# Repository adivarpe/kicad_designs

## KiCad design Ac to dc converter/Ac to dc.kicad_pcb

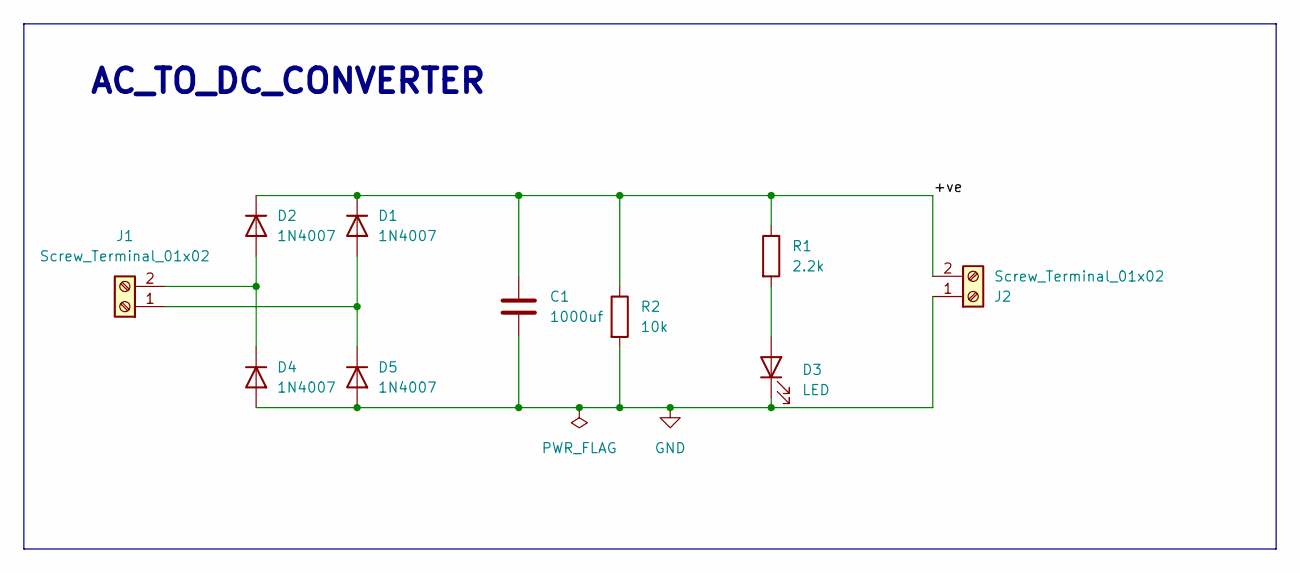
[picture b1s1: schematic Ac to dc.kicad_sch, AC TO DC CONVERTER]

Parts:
C1: 1000uf; CP_Radial_D4.0mm_P2.00mm
D1, D2, D4, D5: 1N4007; D_DO-41_SOD81_P10.16mm_Horizontal
D3: LED; LED_D3.0mm
J1, J2: Screw_Terminal_01x02; TerminalBlock_4Ucon_1x02_P3.50mm_Vertical
R1: 2.2k; R_Axial_DIN0207_L6.3mm_D2.5mm_P10.16mm_Horizontal
R2: 10k; R_Axial_DIN0207_L6.3mm_D2.5mm_P10.16mm_Horizontal

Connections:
/+ve: C1.1, D1.1 (K), D2.1 (K), J2.2, R1.1, R2.1
GND: C1.2, D3.1 (K), D4.2 (A), D5.2 (A), J2.1, R2.2
unnamed: D1.2 (A), D5.1 (K), J1.1
unnamed: D2.2 (A), D4.1 (K), J1.2
unnamed: D3.2 (A), R1.2

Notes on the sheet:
AC_TO_DC_CONVERTER

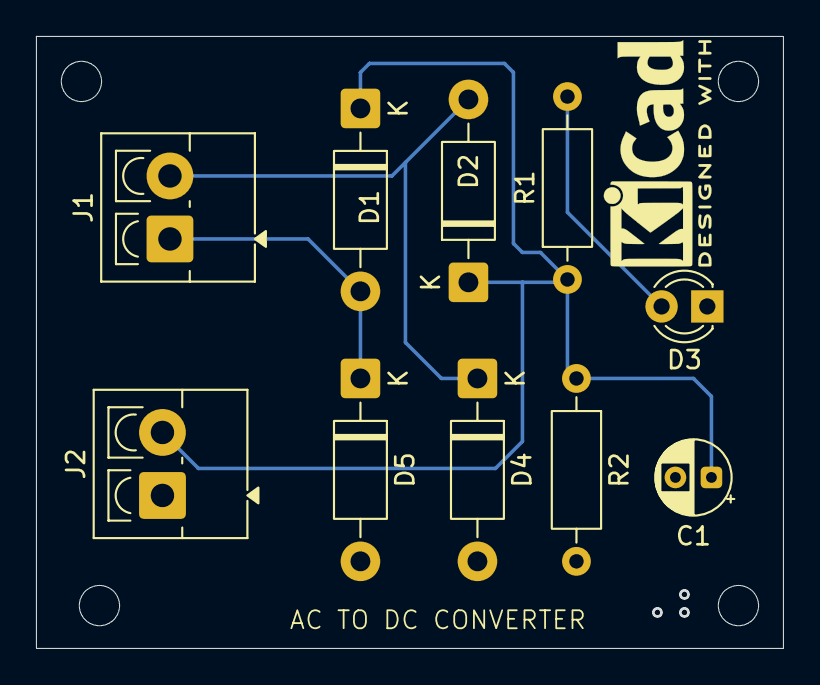
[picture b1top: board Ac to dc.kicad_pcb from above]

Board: 2 copper layers, 41.5 x 34.0 mm, 10 parts (0 on the bottom side), 5 nets.
